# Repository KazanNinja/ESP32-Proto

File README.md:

Proof of concept ESP32-Proto board code.

Currently grabs gear position, engine speed, coolant temperature, and pit limiter switch through CAN and does magical electric stuff with it.

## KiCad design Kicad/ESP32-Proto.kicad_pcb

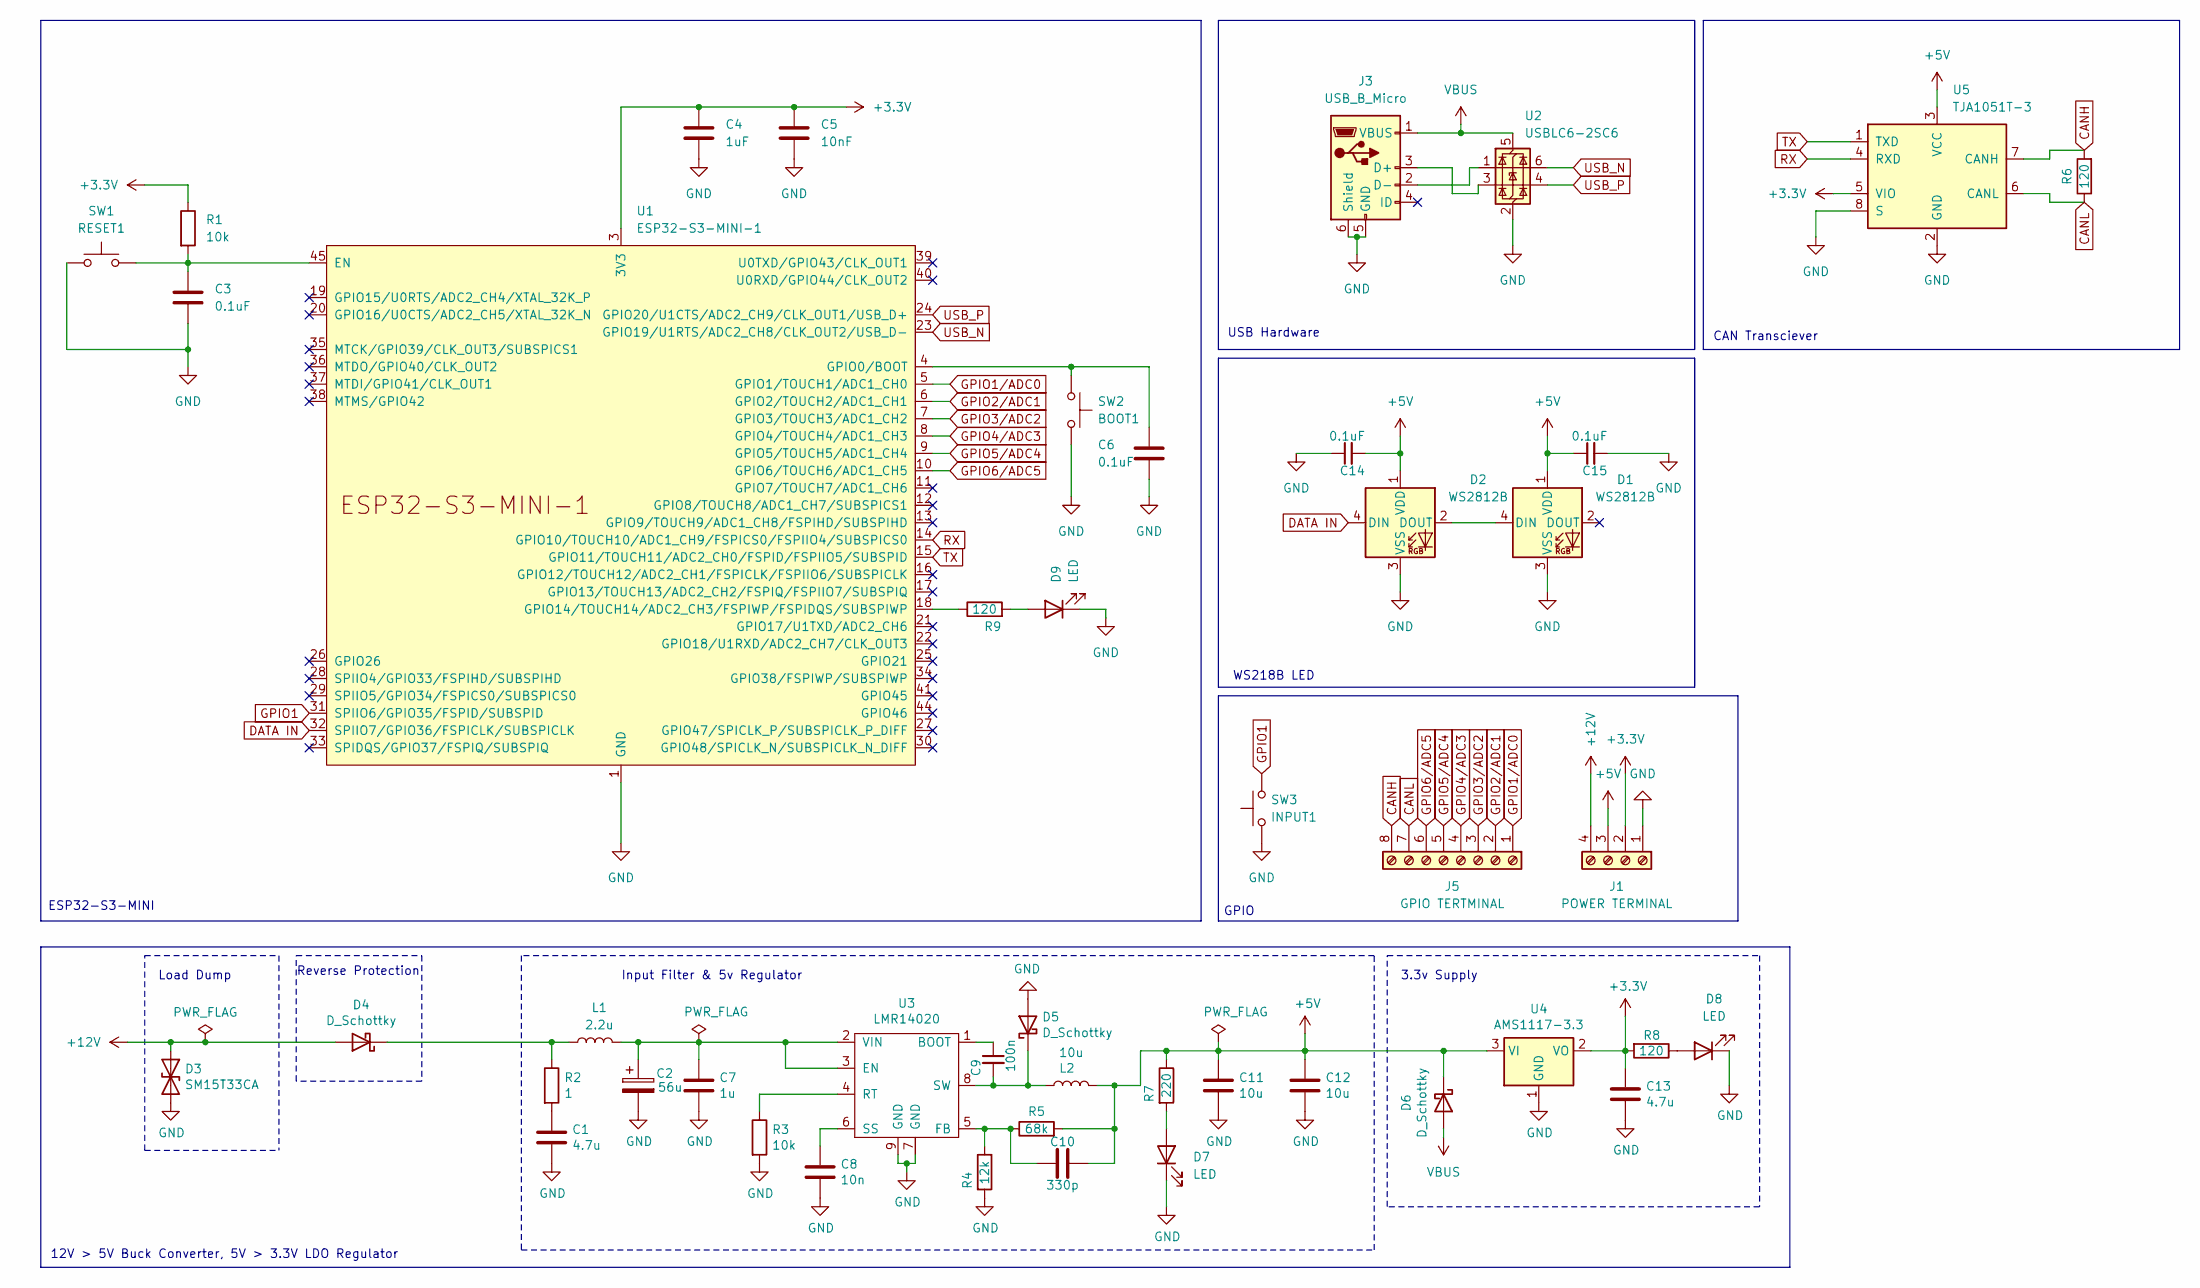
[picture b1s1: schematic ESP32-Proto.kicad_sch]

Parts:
C1, C13: 4.7u; C_0603_1608Metric; LCSC C19666
C2: 56u; CP_Radial_D8.0mm_P2.50mm
C3, C6: 0.1uF; C_0603_1608Metric
C4: 1uF; C_0603_1608Metric
C5: 10nF; C_0603_1608Metric
C7: 1u; C_0603_1608Metric; LCSC C15849
C8: 10n; C_0603_1608Metric; LCSC C57112
C9: 100n; C_0603_1608Metric; LCSC C14663
C10: 330p; C_0603_1608Metric; LCSC C1664
C11, C12: 10u; C_1206_3216Metric; LCSC C13585
C14, C15: 0.1uF; C_0603_1608Metric; LCSC C14663
D1, D2: WS2812B; LED_WS2812B_PLCC4_5.0x5.0mm_P3.2mm
D3: SM15T33CA; D_SMC; LCSC C151281
D4, D5, D6: D_Schottky; D_SMA; LCSC C8678
D7, D8, D9: LED; LED_0805_2012Metric; JLCPCB C2297
J1: POWER TERMINAL; TerminalBlock_Phoenix_MKDS-1,5-4_1x04_P5.00mm_Horizontal
J3: USB_B_Micro; USB_Micro-B_Amphenol_10103594-0001LF_Horizontal
J5: GPIO TERTMINAL; TerminalBlock_Phoenix_PT-1,5-8-3.5-H_1x08_P3.50mm_Horizontal
L1: 2.2u; L_1210_3225Metric; LCSC C286757
L2: 10u; L_Sunlord_MWSA0503S; LCSC C408412
R1: 10k; R_0603_1608Metric
R2: 1; R_0603_1608Metric; LCSC C22936
R3: 10k; R_0603_1608Metric; LCSC C25804
R4: 12k; R_0603_1608Metric; LCSC C22790
R5: 68k; R_0603_1608Metric; LCSC C23231
R6, R8, R9: 120; R_0603_1608Metric; LCSC C22787
R7: 220; R_0603_1608Metric; LCSC C22962
SW1: RESET1; SW_SPST_TL3342
SW2: BOOT1; SW_SPST_TL3342
SW3: INPUT1; SW_SPST_TL3342
U1: ESP32-S3-MINI-1; ESP32-S3-MINI-1U
U2: USBLC6-2SC6; SOT-23-6
U3: LMR14020; SOIC-8-1EP_3.9x4.9mm_P1.27mm_EP2.29x3mm; LCSC C187824
U4: AMS1117-3.3; SOT-223-3_TabPin2; LCSC C6186
U5: TJA1051T-3; SOIC-8_3.9x4.9mm_P1.27mm

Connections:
+3.3V: C4.1, C5.1, C13.1, J1.2, R1.1, R8.2, U1.3 (3V3), U4.2 (VO), U5.5 (VIO)
+5V: C10.1, C11.1, C12.1, C14.2, C15.1, D1.1 (VDD), D2.1 (VDD), D6.1 (K), J1.3, L2.2, R5.2, R7.1, U4.3 (VI), U5.3 (VCC)
+12V: D3.1 (A1), D4.2 (A), J1.4
CANH: J5.8, R6.2, U5.7 (CANH)
CANL: J5.7, R6.1, U5.6 (CANL)
DATA IN: D2.4 (DIN), U1.32 (SPIIO7/GPIO36/FSPICLK/SUBSPICLK)
GND: C1.2, C2.2, C3.2, C4.2, C5.2, C6.2, C7.2, C8.2, C11.2, C12.2, C13.2, C14.1, C15.2, D1.3 (VSS), D2.3 (VSS), D3.2 (A2), D5.2 (A), D7.1 (K), D8.1 (K), D9.1 (K), J1.1, J3.5 (GND), J3.6 (Shield), R3.2, R4.2, SW1.2, SW2.2, SW3.1, U1.1 (GND), U1.2 (GND), U1.42 (GND), U1.43 (GND), U1.46 (GND), U1.47 (GND), U1.48 (GND), U1.49 (GND), U1.50 (GND), U1.51 (GND), U1.52 (GND), U1.53 (GND), U1.54 (GND), U1.55 (GND), U1.56 (GND), U1.57 (GND), U1.58 (GND), U1.59 (GND), U1.60 (GND), U1.61 (GND), U1.62 (GND), U1.63 (GND), U1.64 (GND), U1.65 (GND), U2.2 (GND), U3.7 (GND), U3.9 (GND), U4.1 (GND), U5.2 (GND), U5.8 (S)
GPIO1: SW3.2, U1.31 (SPIIO6/GPIO35/FSPID/SUBSPID)
GPIO1/ADC0: J5.1, U1.5 (GPIO1/TOUCH1/ADC1_CH0)
GPIO2/ADC1: J5.2, U1.6 (GPIO2/TOUCH2/ADC1_CH1)
GPIO3/ADC2: J5.3, U1.7 (GPIO3/TOUCH3/ADC1_CH2)
GPIO4/ADC3: J5.4, U1.8 (GPIO4/TOUCH4/ADC1_CH3)
GPIO5/ADC4: J5.5, U1.9 (GPIO5/TOUCH5/ADC1_CH4)
GPIO6/ADC5: J5.6, U1.10 (GPIO6/TOUCH6/ADC1_CH5)
unnamed: C1.1, R2.2
unnamed: D1.4 (DIN), D2.2 (DOUT)
unnamed: D4.1 (K), L1.1, R2.1
unnamed: C9.2, D5.1 (K), L2.1, U3.8 (SW)
unnamed: D7.2 (A), R7.2
unnamed: D8.2 (A), R8.1
unnamed: D9.2 (A), R9.2
unnamed: J3.3 (D+), U2.3 (I/O2)
unnamed: J3.2 (D-), U2.1 (I/O1)
unnamed: C3.1, R1.2, SW1.1, U1.45 (EN)
unnamed: C6.1, SW2.1, U1.4 (GPIO0/BOOT)
unnamed: R9.1, U1.18 (GPIO14/TOUCH14/ADC2_CH3/FSPIWP/FSPIDQS/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)
unnamed: C9.1, U3.1 (BOOT)
unnamed: C2.1, C7.1, L1.2, U3.2 (VIN), U3.3 (EN)
unnamed: C10.2, R4.1, R5.1, U3.5 (FB)
unnamed: R3.1, U3.4 (RT)
unnamed: C8.1, U3.6 (SS)
RX: U1.14 (GPIO10/TOUCH10/ADC1_CH9/FSPICS0/FSPIIO4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), U5.4 (RXD)
TX: U1.15 (GPIO11/TOUCH11/ADC2_CH0/FSPID/FSPIIO5/S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), U5.1 (TXD)
USB_N: U1.23 (GPIO19/U1RTS/ADC2_CH8/CLK_OUT2/USB_D-), U2.6 (I/O1)
USB_P: U1.24 (GPIO20/U1CTS/ADC2_CH9/CLK_OUT1/USB_D+), U2.4 (I/O2)
VBUS: D6.2 (A), J3.1 (VBUS), U2.5 (VBUS)

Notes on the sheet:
GPIO
Input Filter & 5v Regulator
Reverse Protection
WS218B LED
3.3v Supply
12V > 5V Buck Converter, 5V > 3.3V LDO Regulator
Load Dump
ESP32-S3-MINI
CAN Transciever
USB Hardware

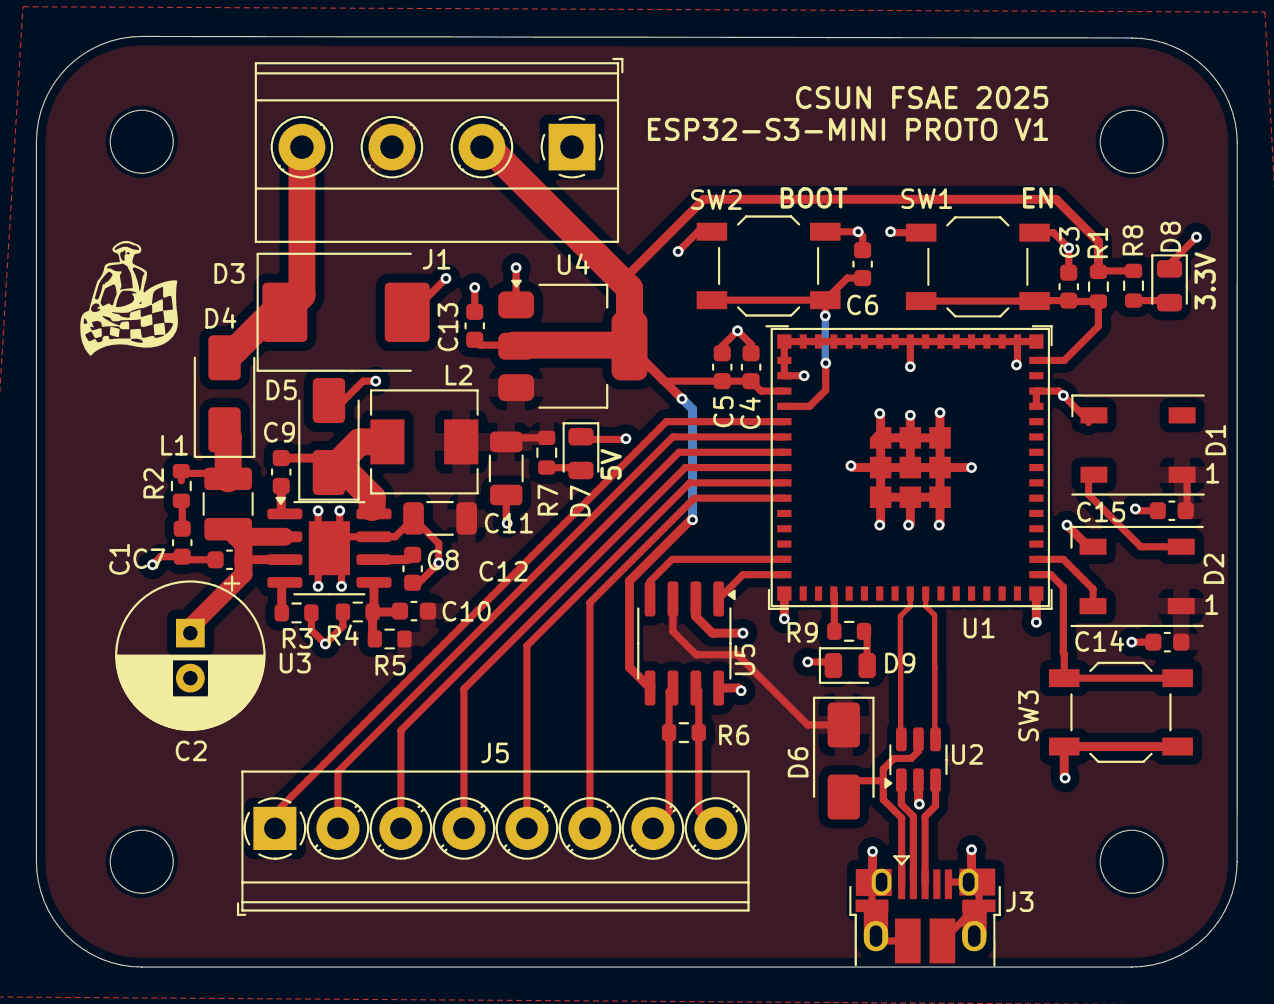
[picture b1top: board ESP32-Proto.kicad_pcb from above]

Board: 2 copper layers, 66.7 x 51.7 mm, 46 parts (0 on the bottom side), 36 nets.

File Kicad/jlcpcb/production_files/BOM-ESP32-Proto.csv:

Comment,Designator,Footprint,LCSC,Quantity
56u,C2,CP_Radial_D8.0mm_P2.50mm,C106629,1
10u,"C11,C12",C_1206_3216Metric,C13585,2
0.1uF,"C14,C15,C3,C6,C9",C_0603_1608Metric,C14663,5
SM15T33CA,D3,D_SMC,C151281,1
1uF,"C4,C7",C_0603_1608Metric,C15849,2
330p,C10,C_0603_1608Metric,C1664,1
LMR14020,U3,SOIC-8-1EP_3.9x4.9mm_P1.27mm_EP2.29x3mm,C187824,1
POWER TERMINAL,J1,"TerminalBlock_Phoenix_MKDS-1,5-4_1x04_P5.00mm_Horizontal",C192769,1
4.7u,"C1,C13",C_0603_1608Metric,C19666,2
120,"R6,R8,R9",R_0603_1608Metric,C22787,3
12k,R4,R_0603_1608Metric,C22790,1
1,R2,R_0603_1608Metric,C22936,1
220,R7,R_0603_1608Metric,C22962,1
LED,"D7,D8,D9",LED_0805_2012Metric,C2297,3
68k,R5,R_0603_1608Metric,C23231,1
10k,"R1,R3",R_0603_1608Metric,C25804,2
WS2812B,"D1,D2",LED_WS2812B_PLCC4_5.0x5.0mm_P3.2mm,C2761795,2
2.2u,L1,L_1210_3225Metric,C286757,1
ESP32-S3-MINI-1,U1,ESP32-S3-MINI-1U,C2980299,1
RESET1,"SW1,SW2,SW3",SW_SPST_TL3342,C318884,3
10u,L2,L_Sunlord_MWSA0503S,C408412,1
USB_B_Micro,J3,USB_Micro-B_Amphenol_10103594-0001LF_Horizontal,C428495,1
TJA1051T-3,U5,SOIC-8_3.9x4.9mm_P1.27mm,C5342108,1
GPIO TERTMINAL,J5,"TerminalBlock_Phoenix_PT-1,5-8-3.5-H_1x08_P3.50mm_Horizontal",C5349548,1
10nF,"C5,C8",C_0603_1608Metric,C57112,2
AMS1117-3.3,U4,SOT-223-3_TabPin2,C6186,1
USBLC6-2SC6,U2,SOT-23-6,C7519,1
D_Schottky,"D4,D5,D6",D_SMA,C8678,3

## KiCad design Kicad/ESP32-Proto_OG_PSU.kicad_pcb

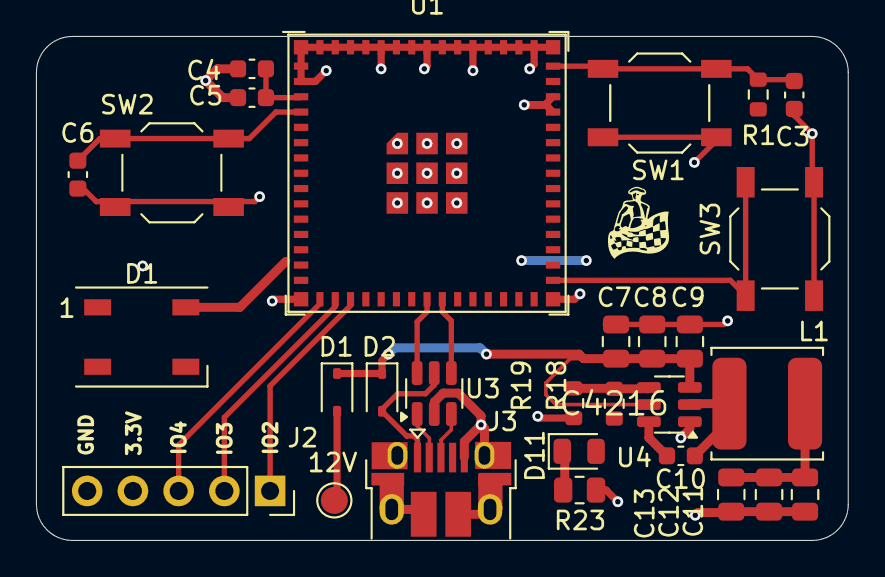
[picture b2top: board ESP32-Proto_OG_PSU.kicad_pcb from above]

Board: 2 copper layers, 45.1 x 28.0 mm, 29 parts (0 on the bottom side), 19 nets.

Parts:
12V: TestPoint_Pad_D1.5mm
C3, C6: 0.1uF; C_0603_1608Metric
C4: 1uF; C_0603_1608Metric
C5: 10nF; C_0603_1608Metric
C7: 0.1uF; C_0805_2012Metric
C8, C9: 10uF; C_0805_2012Metric
C10: 100nF; C_0603_1608Metric
C11, C12, C13: 22uF; C_0805_2012Metric
D1, D2: D_Schottky; D_SOD-323
D1#2: WS2812B; LED_WS2812B_PLCC4_5.0x5.0mm_P3.2mm
D11: LED; LED_0805_2012Metric
J2: Conn_01x05_Pin; PinSocket_1x05_P2.54mm_Vertical
J3: USB_B_Micro; USB_Micro-B_Amphenol_10103594-0001LF_Horizontal
L1: 3.3uH; L_TDK_VLS6045EX_VLS6045AF
R1, R19: 10k; R_0603_1608Metric
R18: 33k; R_0603_1608Metric
R23: 100; R_0805_2012Metric
SW1: RESET1; SW_SPST_TL3342
SW2: BOOT1; SW_SPST_TL3342
SW3: INPUT1; SW_SPST_TL3342
U1: ESP32-S3-MINI-1; ESP32-S3-MINI-1U
U3: USBLC6-2SC6; SOT-23-6
U4: TPS562200; SOT-23-6

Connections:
+3.3V: C4.1, C5.1, C11.1, C12.1, C13.1, D11.2 (A), J2.4, L1.2, R1.1, R18.2, U1.3 (3V3)
+12V: 12V.1, D1.2 (A)
GND: C3.2, C4.2, C5.2, C6.2, C7.2, C8.2, C9.2, C11.2, C12.2, C13.2, D1#2.3 (VSS), J2.5, J3.5 (GND), J3.6 (Shield), R19.2, R23.2, SW1.2, SW2.2, SW3.1, U1.1 (GND), U1.2 (GND), U1.42 (GND), U1.43 (GND), U1.46 (GND), U1.47 (GND), U1.48 (GND), U1.49 (GND), U1.50 (GND), U1.51 (GND), U1.52 (GND), U1.53 (GND), U1.54 (GND), U1.55 (GND), U1.56 (GND), U1.57 (GND), U1.58 (GND), U1.59 (GND), U1.60 (GND), U1.61 (GND), U1.62 (GND), U1.63 (GND), U1.64 (GND), U1.65 (GND), U3.2 (GND), U4.1 (GND)
GPIO1: SW3.2, U1.31 (SPIIO6/GPIO35/FSPID/SUBSPID)
GPIO2: J2.1, U1.18 (GPIO14/TOUCH14/ADC2_CH3/FSPIWP/FSPIDQS/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)
GPIO3: J2.2, U1.17 (GPIO13/TOUCH13/ADC2_CH2/FSPIQ/FSPIIO7/S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)
GPIO4: J2.3, U1.16 (GPIO12/TOUCH12/ADC2_CH1/FSPICLK/FSPIIO6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)
unnamed: C7.1, C8.1, C9.1, D1.1 (K), D2.1 (K), U4.3 (VIN), U4.5 (EN)
unnamed: D11.1 (K), R23.1
unnamed: J3.3 (D+), U3.3 (I/O2)
unnamed: J3.2 (D-), U3.1 (I/O1)
unnamed: C3.1, R1.2, SW1.1, U1.45 (EN)
unnamed: C6.1, SW2.1, U1.4 (GPIO0/BOOT)
unnamed: C10.1, L1.1, U4.2 (SW)
unnamed: C10.2, U4.6 (VBST)
unnamed: R18.1, R19.1, U4.4 (VFB)
USB_N: U1.23 (GPIO19/U1RTS/ADC2_CH8/CLK_OUT2/USB_D-), U3.6 (I/O1)
USB_P: U1.24 (GPIO20/U1CTS/ADC2_CH9/CLK_OUT1/USB_D+), U3.4 (I/O2)
VBUS: D2.2 (A), J3.1 (VBUS), U3.5 (VBUS)

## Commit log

2024-12-22 Test Commit
    Testing, TESSTTIIINNNGG, AHHHHHHH
2024-12-22 Large Formatting and Cleanup
    Removed many unused lines of code. Cleaned up formatting
2024-12-22 More formatting and cleanup
    Cleaned some comments, removed some stuff, the usual
2024-12-23 Stuff
2024-12-24 Added/Removed Features
    Removed gear switch statement, added RPM fade light thing.
2025-08-27 Kicad Files
